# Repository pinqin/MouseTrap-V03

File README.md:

# MouseTrap-V03
ESP32 Pico D4 Board with 
- VSPI-Connector
- SMA antenna Connector
- 3 Switches ...
  - IO0 (ESP32)
  - EN (ESP32)
  - MOD (Free to use)
- SD-Card Slot

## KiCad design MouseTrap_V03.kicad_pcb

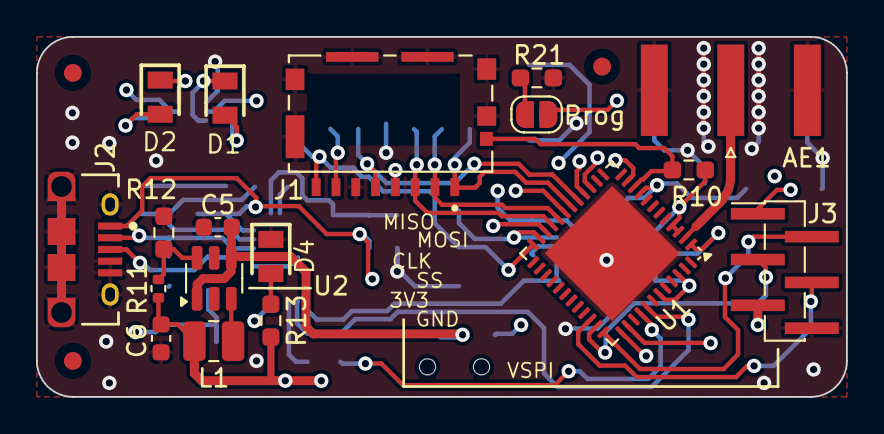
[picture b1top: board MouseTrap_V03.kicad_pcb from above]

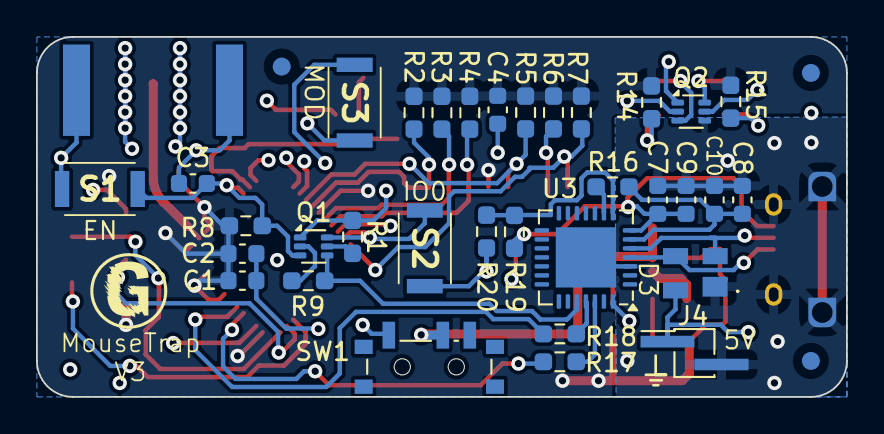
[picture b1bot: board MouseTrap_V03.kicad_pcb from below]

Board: 4 copper layers, 45.0 x 20.0 mm, 57 parts (36 on the bottom side), 42 nets.

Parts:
AE1: Antenna_Shield; SMA_Amphenol_132289_EdgeMount
C1, C4: 10µF X5R 25V; C_0603_1608Metric
C2, C3, C7, C8: 100nF; C_0603_1608Metric
C5, C6: 22µ; C_0603_1608Metric
C9, C10: 4.7µF; C_0603_1608Metric
D1: HSMG-C170; LEDC2012X80N
D2: HSMB-C170; LEDC2012X80N
D3: SP0503BAHTG
D4: HSMS-C170; LEDC2012X80N
FID1, FID2, FID3, FID4, FID5, FID6: Fiducial; Fiducial_1mm_Mask2mm
J1: 1051620001
J2: 10118194-0001LF; Amphenol_ICC-10118194-0001LF-MFG
J3: Conn_01x06_Socket; PinHeader_1x06_P1.27mm_Vertical_SMD_Pin1Left
J4: Conn_01x02_Pin; PinHeader_1x02_P1.27mm_Vertical_SMD_Pin1Left
JP1: Jumper_2_Open; SolderJumper-2_P1.3mm_Open_RoundedPad1.0x1.5mm
L1: 2µ2; L_1008_2520Metric
Q1, Q2: DMN63D8LV-7; SOT-563
R1, R9: 2K2; R_0603_1608Metric_Pad0.98x0.95mm_HandSolder
R2, R3, R4, R5, R6, R7, R8, R10: 10K; R_0603_1608Metric_Pad0.98x0.95mm_HandSolder
R11: 450K; R_0402_1005Metric
R12: 100K; R_0603_1608Metric_Pad0.98x0.95mm_HandSolder
R13, R14, R15, R17, R18, R21: 1K; R_0603_1608Metric_Pad0.98x0.95mm_HandSolder
R16: 4K7; R_0603_1608Metric_Pad0.98x0.95mm_HandSolder
R19: 22K6; R_0603_1608Metric_Pad0.98x0.95mm_HandSolder
R20: 47K; R_0603_1608Metric_Pad0.98x0.95mm_HandSolder
S1, S2, S3: SKRKAEE020
SW1: SW_DIP_x01; SW_SPDT_PCM12
U1: ESP32-PICO-D4; QFN-48-1EP_7x7mm_P0.5mm_EP5.3x5.3mm
U2: MT3420C-mt3420c; SOT-23-6
U3: CP2102N-Axx-xQFN28; QFN-28-1EP_5x5mm_P0.5mm_EP3.35x3.35mm

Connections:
ChangeModi: S3.1, U1.11 (IO35)
DTR: Q1.1 (S2), R1.2, U3.28 (~DTR)
EN: C3.2, Q1.3 (D1), R8.1, S1.1, U1.9 (EN)
EN_LED_BLUE: Q2.2 (G2), U1.15 (IO26)
EN_LED_GREEN: Q2.5 (G1), U1.16 (IO27)
ESD_K1: D3.2 (K_1), J2.2, U3.5 (D-)
ESD_K2: D3.3 (K_2), J2.3, U3.4 (D+)
ESD_K3: C7.2, C9.2, D3.4 (K_3), J2.1, J4.1, R19.1, SW1.1, U3.7 (VREGIN)
GND: AE1.2 (Shield), C1.2, C2.2, C3.1, C4.2, C5.2, C6.2, C7.1, C8.2, C9.1, C10.2, D3.1 (COMMON_A), D4.1, J1.6 (VSS), J1.10 (GND), J1.11 (GND), J1.12 (SHIELD), J1.13 (SHIELD), J1.14 (GND), J1.15 (GND), J2.4, J2.5, J2.6 (MNT_1), J2.7 (MNT_2), J2.8 (MNT_3), J2.9 (MNT_4), J2.10 (MNT_5), J2.11 (MNT_6), J3.6, J4.2, Q2.1 (S2), Q2.4 (S1), R12.2, R20.2, R21.1, S1.2, S2.2, S3.2, U1.49 (GND), U2.2 (GND), U3.3 (GND), U3.29 (GND)
GPIO0: Q1.6 (D2), S2.1, U1.23 (IO0)
unnamed: AE1.1 (A), U1.2 (LNA_IN)
unnamed: D1.2 (A), R14.2
unnamed: D1.1 (K), Q2.3 (D1)
unnamed: D2.2 (A), R15.2
unnamed: D2.1 (K), Q2.6 (D2)
unnamed: D4.2, R13.1
unnamed: JP1.1 (A), R21.2
unnamed: Q1.5 (G1), R1.1
unnamed: Q1.2 (G2), R9.1
unnamed: C5.1, SW1.2, U2.1 (EN), U2.4 (IN)
unnamed: R11.2, R12.1, U2.6 (FB)
unnamed: L1.1, U2.3 (SW)
unnamed: R18.1, U3.25 (RXD)
unnamed: R17.1, U3.26 (TXD)
unnamed: C8.1, C10.1, R16.1, U3.6 (VDD)
unnamed: R16.2, U3.9 (~RST)
RTS: Q1.4 (S1), R9.2, U3.24 (~RTS)
RXD0: R17.2, U1.40 (U0RXD/IO3)
SD0: J1.7 (DAT0), JP1.2 (B), R6.1, U1.22 (IO2)
SD1: J1.8 (DAT1), R7.1, U1.24 (IO4)
SD2: J1.1 (DAT2), R2.1, U1.18 (IO12)
SD3: J1.2 (DAT3/CD), R3.1, U1.20 (IO13)
SD_CD: J1.9 (DET), R10.1, U1.10 (IO34)
SD_CLK: J1.5 (CLK), R5.1, U1.17 (IO14)
SD_CMD: J1.3 (CMD), R4.1, U1.21 (IO15)
TXD0: R18.2, U1.41 (U0TXD/IO1)
VBUS: R19.2, R20.1, U3.8 (VBUS)
VDD 3V3: C1.1, C2.1, C4.1, C6.1, J1.4 (VDD), J3.5, L1.2, R2.2, R3.2, R4.2, R5.2, R6.2, R7.2, R8.2, R10.2, R11.1, R13.2, R14.1, R15.1, U1.1 (VDDA), U1.3 (VDDA3P3), U1.4 (VDDA3P3), U1.19 (VDD3P3_RTC), U1.37 (VDD3P3_CPU), U1.43 (VDDA), U1.46 (VDDA)
VSPI_MISO: J3.1, U1.38 (IO19)
VSPI_MOSI: J3.2, U1.36 (IO23)
VSPI_SCLK: J3.3, U1.35 (IO18)
VSPI_SS: J3.4, U1.34 (IO5)

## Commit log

2025-02-01 Adding Housing
    Adding Housing
